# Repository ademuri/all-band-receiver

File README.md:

# All-band receiver

This is a PCB for the audio amplifier IC version of the [Techlib Amazing All-Band Receiver](http://www.techlib.com/electronics/allband.htm). It is a device that makes the normally-invisible world of RF audible.

"This is not an officially supported Google product"

## Versions

The latest and greatest version is in [low-voltage](low-voltage). This version is powered by 4xAAA, and is relatively simple. This is the one you want to build.

[all-through-hole](all-through-hole) and [audio-rf](audio-rf) contain the previous (overengineered) version, which was powered by a single 18650 lithium-ion battery. It used a boost converter followed by a linear regulator to step the battery voltage up to 9v. This is overkill, and also caused noise issues.

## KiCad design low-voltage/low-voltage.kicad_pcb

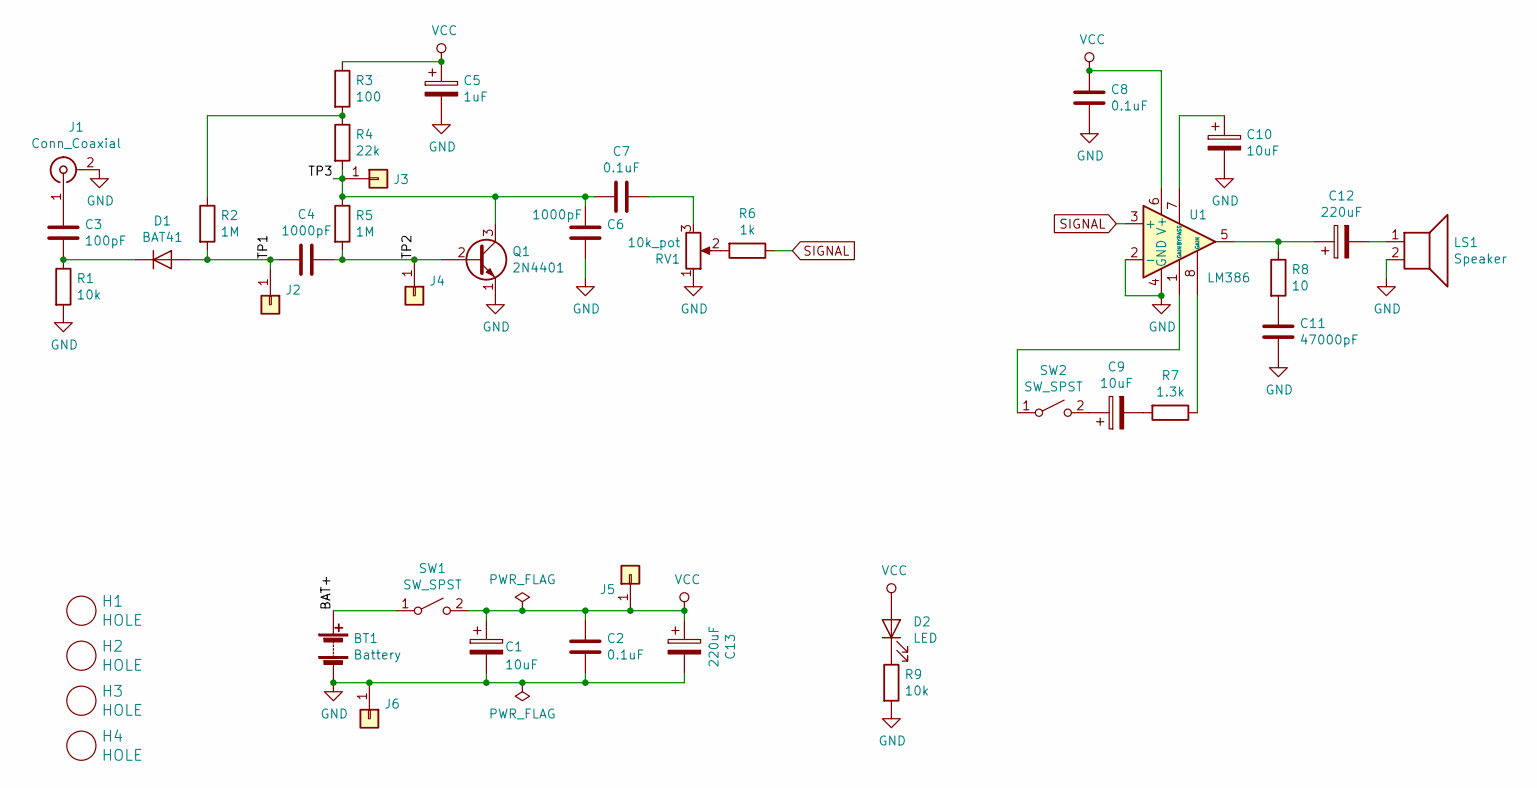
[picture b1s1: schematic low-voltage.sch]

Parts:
BT1: Battery; BatteryHolder_Keystone_2481_4xAAA
C1, C9, C10: 10uF; CP_Radial_D5.0mm_P2.00mm
C2, C7, C8: 0.1uF; C_Disc_D5.1mm_W3.2mm_P5.00mm
C3: 100pF; C_Disc_D5.0mm_W2.5mm_P5.00mm
C4, C6: 1000pF; C_Disc_D5.0mm_W2.5mm_P5.00mm
C5: 1uF; CP_Radial_D5.0mm_P2.00mm
C11: 47000pF; C_Disc_D3.8mm_W2.6mm_P2.50mm
C12, C13: 220uF; CP_Radial_D6.3mm_P2.50mm
D1: BAT41; D_DO-35_SOD27_P7.62mm_Horizontal
D2: LED; LED_D5.0mm_Horizontal_O1.27mm_Z9.0mm
H1, H2, H3, H4: HOLE; HOLE_5MM_#8
J1: Conn_Coaxial; MOLEX_0731713150
J2, J3, J4: Conn_01x01; PinHeader_1x01_P2.54mm_Vertical
J5, J6: Conn_01x01; ALLIGATOR_CLIP_SLOT
LS1: Speaker; CLS0231MP-1_SPEAKER
Q1: 2N4401; TO-92_Inline_Wide
R1, R9: 10k; R_Axial_DIN0207_L6.3mm_D2.5mm_P10.16mm_Horizontal
R2, R5: 1M; R_Axial_DIN0207_L6.3mm_D2.5mm_P10.16mm_Horizontal
R3: 100; R_Axial_DIN0207_L6.3mm_D2.5mm_P10.16mm_Horizontal
R4: 22k; R_Axial_DIN0207_L6.3mm_D2.5mm_P10.16mm_Horizontal
R6: 1k; R_Axial_DIN0207_L6.3mm_D2.5mm_P10.16mm_Horizontal
R7: 1.3k; R_Axial_DIN0207_L6.3mm_D2.5mm_P10.16mm_Horizontal
R8: 10; R_Axial_DIN0207_L6.3mm_D2.5mm_P10.16mm_Horizontal
RV1: 10k_pot; Potentiometer_Bourns_PTV09A-2_Single_Horizontal
SW1, SW2: SW_SPST; ‎EG1206‎_SLIDE_SWITCH
U1: LM386; DIP-8_W7.62mm

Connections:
/BAT+: BT1.1 (+), SW1.1 (A)
/TP1: C4.2, D1.2 (A), J2.1, R2.2
/TP2: C4.1, J4.1, Q1.2 (B), R5.2
/TP3: C6.1, C7.2, J3.1, Q1.3 (C), R4.2, R5.1
GND: BT1.2 (-), C1.2, C2.2, C5.2, C6.2, C8.2, C10.2, C11.2, C13.2, J1.2 (Ext), J6.1, LS1.2, Q1.1 (E), R1.2, R9.2, RV1.1, U1.2 (-), U1.4 (GND)
unnamed: C3.1, J1.1 (In)
unnamed: C3.2, D1.1 (K), R1.1
unnamed: C7.1, RV1.3
unnamed: C9.1, SW2.2 (B)
unnamed: C9.2, R7.2
unnamed: C10.1, U1.7 (BYPASS)
unnamed: C11.1, R8.2
unnamed: C12.1, R8.1, U1.5
unnamed: C12.2, LS1.1
unnamed: D2.1 (K), R9.1
unnamed: R2.1, R3.2, R4.1
unnamed: R6.2, RV1.2
unnamed: R7.1, U1.8 (GAIN)
unnamed: SW2.1 (A), U1.1 (GAIN)
SIGNAL: R6.1, U1.3 (+)
VCC: C1.1, C2.1, C5.1, C8.1, C13.1, D2.2 (A), J5.1, R3.1, SW1.2 (B), U1.6 (V+)

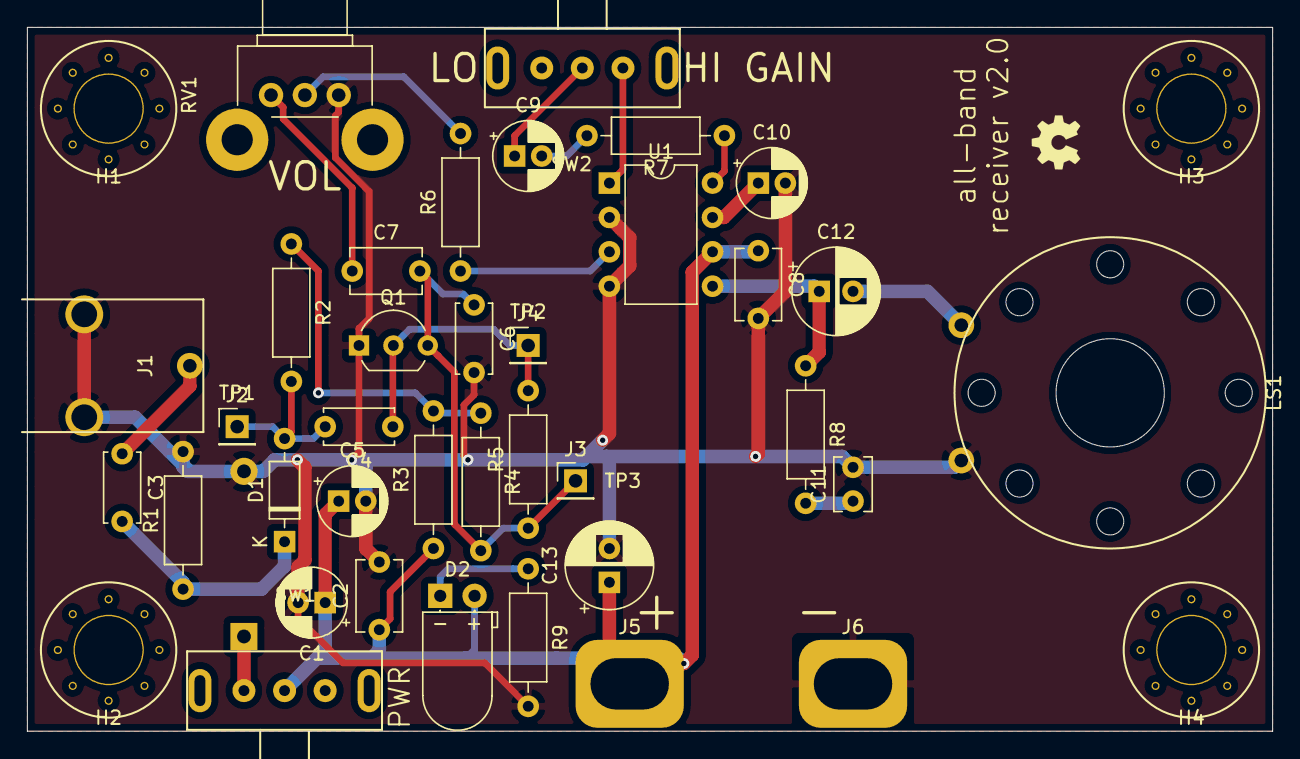
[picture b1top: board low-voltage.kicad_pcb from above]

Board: 2 copper layers, 92.0 x 52.0 mm, 41 parts (1 on the bottom side), 21 nets.

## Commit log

2020-03-25 Add rf/audio, start adding power supply
2020-03-25 Add license, contributing, and README disclaimer
2020-03-27 First pass at all-through-hole schematic
2020-03-27 First pass at layout
2020-03-27 Associate footprints for all-through-hole
2020-03-27 Hardware v1.0
2020-04-03 Add interactive bom for all-through-hole v1.0
2020-04-04 Remove unused partial-semd
2020-04-14 Add a schematic for a low-voltage version.
    PCB and BOM are not complete.
2020-04-19 Change low voltage to use lm386 instead of njm2113
2020-04-21 Place components for low voltage
2020-04-24 Final design for low voltage (v2.0)
2020-05-03 Add BOM and update README
2020-08-01 Add 3d model for pot
2020-08-02 Add 3d models for BNC connector and slide switch
2020-08-02 Add 3d model for low voltage board
2020-08-02 Add case STL files
2020-08-02 Add finger catch and pcb mount bumps to case top
